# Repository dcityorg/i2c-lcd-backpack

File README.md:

#### I²C LCD Backpack Board for character LCD modules

<div style="text-align: center;">
<div style="display: inline-block; margin-right: 5px;">

</div>
<div style="display: inline-block; margin-right: 5px;">

</div>
<div style="display: inline-block; margin-right: 5px;">

</div>
</div>

**[This link has details](https://www.dcity.org/portfolio/i2c-lcd-backpack-board/) including**
* parts lists
* assembly instructions
* jumper configuration
* Arduino, Particle and Raspberry Pi software library usage
* Bare PC boards are available from OSHPark.

**License Information**
Open Source Hardware Design. Our License Information is [here](https://www.dcity.org/license-information/).

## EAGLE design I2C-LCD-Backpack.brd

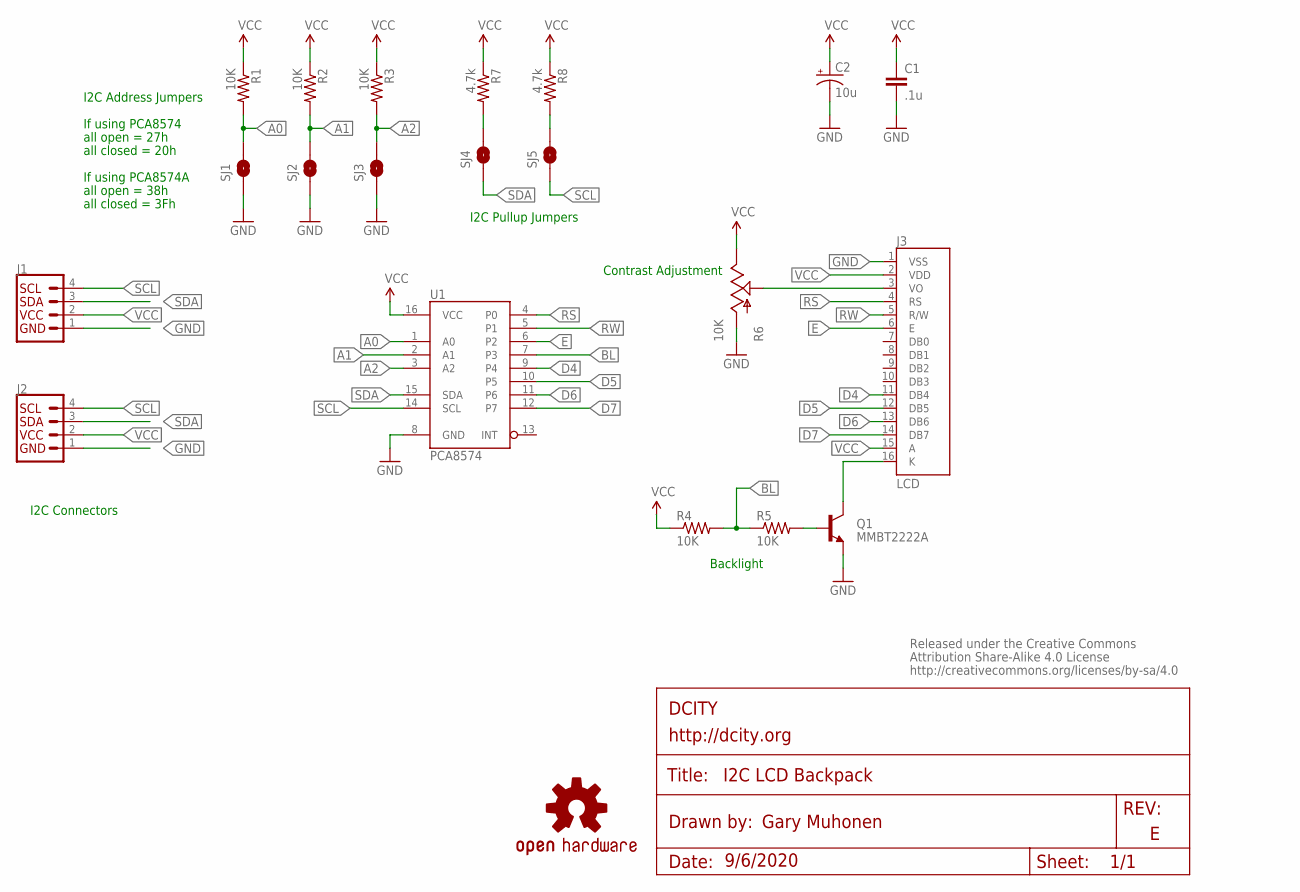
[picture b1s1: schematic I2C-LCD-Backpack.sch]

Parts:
C1: .1u; 0805-CAP
C2: 10u; 0805-POL
J1, J2: QWIIC_RIGHT_ANGLE; JST04_1MM_RA
J3: LCD; 1X16_LOCK
LOGO1: OSHW-LOGOS; OSHW-LOGO-S
Q1: MMBT2222A; SOT23-3
R1, R2, R3, R4, R5: 10K; 0805-RES
R6: 10K; TC33X
R7, R8: 4.7k; 0805-RES
SJ1, SJ2, SJ3, SJ4, SJ5: SOLDERJUMPERNC; SJ_2S
U1: PCA8574; TSSOP16
U$2: CREATIVE_COMMONS

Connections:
A0: R1.2, SJ1.2, U1.1 (A0)
A1: R2.2, SJ2.2, U1.2 (A1)
A2: R3.2, SJ3.2, U1.3 (A2)
BL: R4.2, R5.1, U1.7 (P3)
D4: J3.11 (DB4), U1.9 (P4)
D5: J3.12 (DB5), U1.10 (P5)
D6: J3.13 (DB6), U1.11 (P6)
D7: J3.14 (DB7), U1.12 (P7)
E: J3.6 (E), U1.6 (P2)
GND: C1.2, C2.-, J1.1, J2.1, J3.1 (VSS), Q1.2 (E), R6.1 (A), SJ1.1, SJ2.1, SJ3.1, U1.8 (GND)
unnamed: R7.2, SJ4.2
unnamed: R8.2, SJ5.2
unnamed: Q1.1 (B), R5.2
unnamed: J3.16 (K), Q1.3 (C)
unnamed: J3.3 (VO), R6.2 (S)
RS: J3.4 (RS), U1.4 (P0)
RW: J3.5 (R/W), U1.5 (P1)
SCL: J1.4, J2.4, SJ5.1, U1.14 (SCL)
SDA: J1.3, J2.3, SJ4.1, U1.15 (SDA)
VCC: C1.1, C2.+, J1.2, J2.2, J3.2 (VDD), J3.15 (A), R1.1, R2.1, R3.1, R4.1, R6.3 (E), R7.1, R8.1, U1.16 (VCC)

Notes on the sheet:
If using PCA8574
all open = 27h
all closed = 20h
I2C Connectors
Contrast Adjustment
Backlight
I2C Pullup Jumpers
all closed = 3Fh
all open = 38h
I2C Address Jumpers
If using PCA8574A

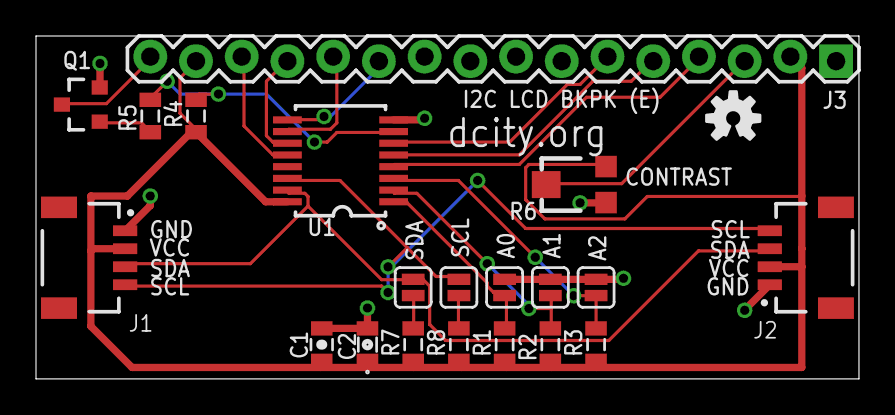
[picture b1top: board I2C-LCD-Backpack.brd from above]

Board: 2 copper layers, 45.7 x 19.1 mm, 22 parts (0 on the bottom side), 20 nets.

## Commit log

2016-04-05 First commit - Rev C
2016-04-13 changed pictures in readme.md
2018-09-14 Rev D
2020-10-11 Rev E

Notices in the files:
parts and their libraries:
0: Released under the Creative Commons
0: http://creativecommons.org/licenses/by-sa/4.0
